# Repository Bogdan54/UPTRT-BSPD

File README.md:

# UPTRT-BSPD PCB Design (Version 1.2)
This repository contains the PCB design files for the UPTRT-BSPD project. The UPTRT-BSPD is being developed for participation in the Formula Student competition.

## Overview
The UPTRT-BSPD PCB is designed to provide brake system plausibility monitoring and control functionalities. The PCB incorporates a microcontroller, flip-flop components, potentiometer, and connectors for external connections. The design ensures reliable and efficient performance while meeting the requirements of the Formula Student competition.

## Repository Structure
* PCB/Using 74HC74N with potentiometer/: Contains the KiCad project files for the PCB design.
* PCB/Using 74HC74N with potentiometer/schematic.png: Schematic diagram in PNG format.
* PCB/Using 74HC74N with potentiometer/bom.csv: Bill of Materials (BOM) listing the components used.
* PCB/Using 74HC74N with potentiometer/gerber/: Gerber files required for PCB manufacturing.

## Getting Started
To view or modify the PCB design, you will need to have KiCad installed on your system. Follow these steps to get started:

1. Clone this repository to your local machine using  
> git clone https://github.com/Bogdan54/UPTRT-BSPD.git
2. Open the KiCad project files located in the PCB/Using 74HC74N with potentiometer/ directory.
3. Use <a href="https://www.kicad.org/">KiCad</a> to view or modify the schematic, layout, and component placement and for the simulation you will have <a href="https://www.ni.com/ro-ro/support/downloads/software-products/download.multisim.html#452133">Multisim 14</a>.
4. Generate the necessary output files, such as Gerber files, for PCB manufacturing.

## Manufacturing
To manufacture the UPTRT-BSPD PCB, follow these steps:

1. Review the manufacturing specifications in the documentation.
2. Generate the required Gerber files using the KiCad project.
3. Submit the Gerber files to your chosen PCB manufacturer.
4. Review the manufactured PCB for quality and ensure it meets the specified dimensions and specifications.

## Documentation
For detailed documentation of the PCB design, including the schematic overview, component selection, layout considerations, and manufacturing specifications, please refer to the documentation files provided in the repository.

## Contributing
Contributions to this project are welcome. If you find any issues or have suggestions for improvements, please open an issue or submit a pull request.

## License
This project is licensed under the <a href="https://www.gnu.org/licenses/gpl-3.0.en.html">GPLv3 License</a>.

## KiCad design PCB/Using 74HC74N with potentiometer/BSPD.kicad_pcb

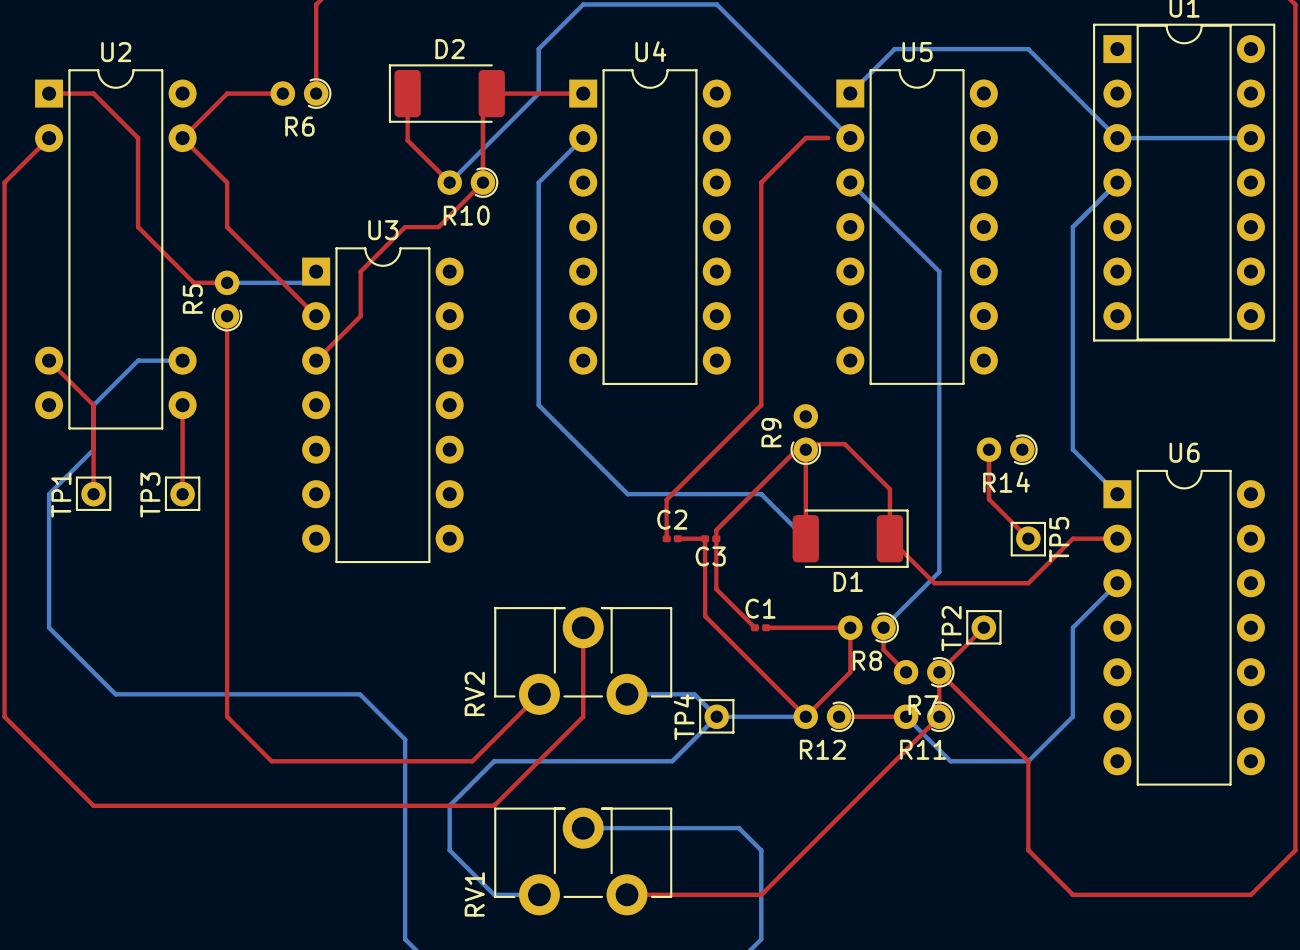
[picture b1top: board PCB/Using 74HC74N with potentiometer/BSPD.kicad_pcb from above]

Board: 2 copper layers, 27 parts (0 on the bottom side), 18 nets.

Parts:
C1, C3: 47uF; C_0201_0603Metric
C2: 470uF; C_0201_0603Metric
D1, D2: DIODE; D_MELF
R5, R6, R9: 10k; R_Axial_DIN0204_L3.6mm_D1.6mm_P1.90mm_Vertical
R7, R8, R11, R12: 1k; R_Axial_DIN0204_L3.6mm_D1.6mm_P1.90mm_Vertical
R10: 20k; R_Axial_DIN0204_L3.6mm_D1.6mm_P1.90mm_Vertical
R14: R; R_Axial_DIN0204_L3.6mm_D1.6mm_P1.90mm_Vertical
RV1, RV2: 10k; Potentiometer_ACP_CA9-H3,8_Horizontal
TP1, TP2, TP3, TP4, TP5: TestPoint; Pin_D0.7mm_L6.5mm_W1.8mm_FlatFork
U1: sn7476n; DIP-14_W7.62mm_Socket
U2: LM393; DIP-8-16_W7.62mm
U3: 4081; DIP-14_W7.62mm
U4: 74HC04; DIP-14_W7.62mm
U5, U6: LM324; DIP-14_W7.62mm

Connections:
unnamed: C1.2, C2.2, C3.2, R8.2, R12.2, RV1.1, RV2.3, TP4.1
unnamed: D1.2 (A), R9.1, U4.2
unnamed: C1.1, C3.1, D1.1 (K), R9.2, U6.2 (-)
unnamed: D2.2 (A), R10.1, U3.3, U4.1
unnamed: C2.1, D2.1 (K), R10.2, U5.2 (-)
unnamed: R5.2, U2.1, U3.1
unnamed: R6.2, U2.7, U3.2
unnamed: R6.1, R7.1, R11.1, RV1.3, TP2.1
unnamed: R14.2, TP5.1
unnamed: U1.3 (CLR), U1.12 (K), U5.1
unnamed: U1.4 (J), U6.1
unnamed: TP1.1, U2.3 (+)
unnamed: RV2.2, U2.2 (-)
unnamed: TP3.1, U2.5 (+)
unnamed: RV1.2, U2.6 (-)
unnamed: R7.2, R8.1, U5.3 (+)
unnamed: R11.2, R12.1, U6.3 (+)
VCC: R5.1, RV2.1, U1.5 (VCC)

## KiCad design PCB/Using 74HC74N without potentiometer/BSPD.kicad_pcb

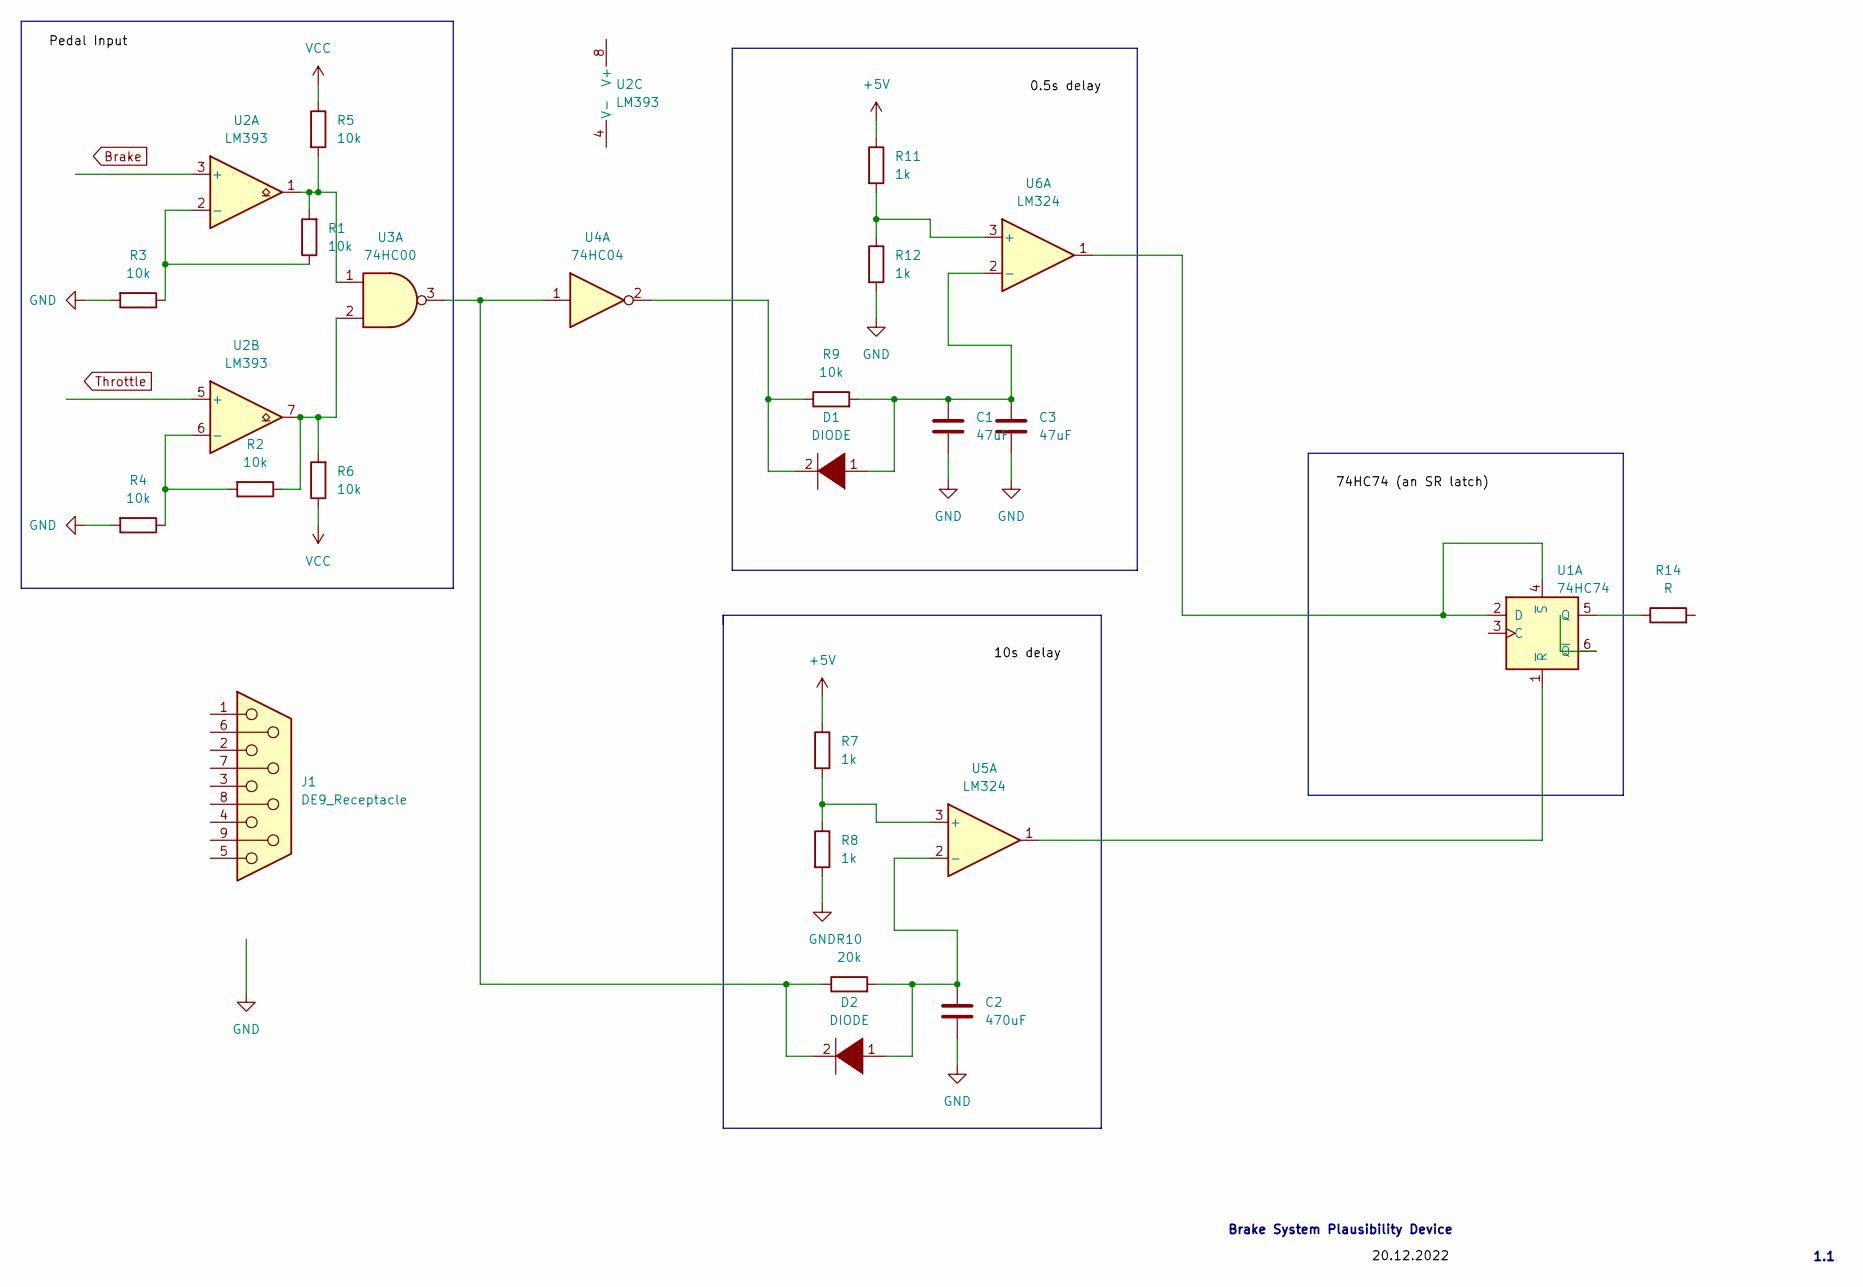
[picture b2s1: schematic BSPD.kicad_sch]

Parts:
C1, C3: 47uF; C_0201_0603Metric
C2: 470uF; C_0201_0603Metric
D1, D2: DIODE; D_MELF
J1: DE9_Receptacle
R1, R2, R3, R4, R5, R6, R9: 10k; R_0201_0603Metric
R7, R8, R11, R12: 1k; R_0201_0603Metric
R10: 20k; R_0201_0603Metric
R14: R; R_0201_0603Metric
U1: 74HC74; DIP-14_W7.62mm
U2: LM393; DIP-8-16_W7.62mm
U3: 74HC00; DIP-14_W7.62mm
U4: 74HC04; DIP-14_W7.62mm
U5, U6: LM324; DIP-14_W7.62mm

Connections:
+5V: R7.1, R11.1; also elsewhere on the board
GND: C1.2, C2.2, C3.2, R3.2, R4.2, R8.2, R12.2
unnamed: D1.2 (A), R9.1, U4.2
unnamed: C1.1, C3.1, D1.1 (K), R9.2, U6.2 (-)
unnamed: D2.2 (A), R10.1, U3.3, U4.1
unnamed: C2.1, D2.1 (K), R10.2, U5.2 (-)
unnamed 7: R14.2; also elsewhere on the board
unnamed: R1.2, R5.2, U2.1, U3.1
unnamed: R2.1, R6.2, U2.7, U3.2
unnamed: U1.2 (D), U1.4 (~S), U6.1
unnamed: R14.1, U1.5 (Q)
unnamed: U1.1 (~R), U5.1
unnamed: R1.1, R3.1, U2.2 (-)
unnamed: R2.2, R4.1, U2.6 (-)
unnamed: R7.2, R8.1, U5.3 (+)
unnamed: R11.2, R12.1, U6.3 (+)
VCC: R5.1, R6.1

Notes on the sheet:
Brake System Plausibility Device
1.1

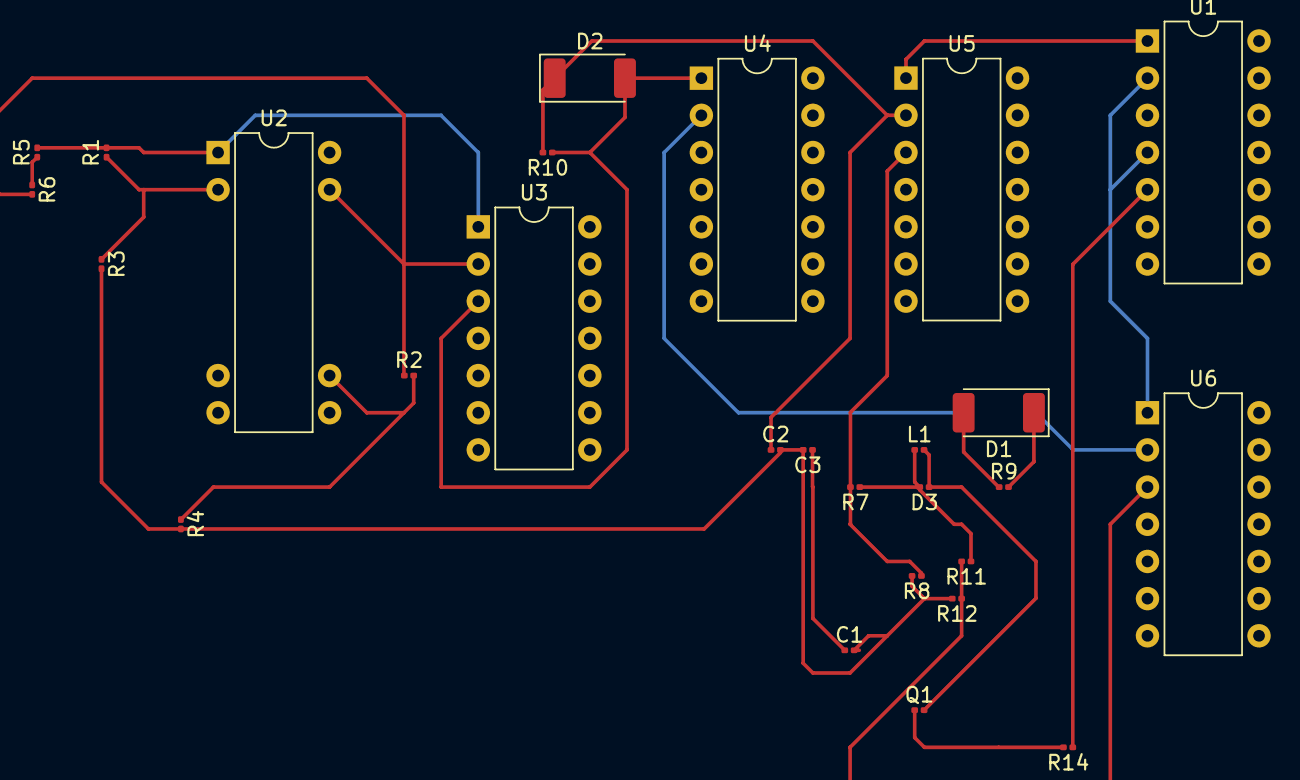
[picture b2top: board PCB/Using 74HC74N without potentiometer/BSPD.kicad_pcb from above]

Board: 2 copper layers, 27 parts (0 on the bottom side), 18 nets.

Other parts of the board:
D3: DIODE; R_0201_0603Metric
L1: L; R_0201_0603Metric
Q1: IRLZ34N; R_0201_0603Metric

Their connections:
+5V: D3.2 (A), L1.1; also elsewhere on the board
unnamed: D3.1 (K), L1.2, Q1.2 (D)
unnamed 7: Q1.1 (G); also elsewhere on the board

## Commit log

2023-03-06 Adding stuff
    Adding schematic, kicad project and simulation
2023-04-12 Adding Final Changes
    Adding Final Changes Using NE555p timer.
2023-04-12 Adding the BSPD with flip-flop
2023-04-26 26.04.2023
2023-05-23 Create LICENSE
